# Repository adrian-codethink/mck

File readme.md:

# Modular choc Keeb

This is an attempt to make a 3 key module to allow custom angle and spacing of a column staggered ergonomic keyboard.

Initially this will make it relatively simple to string 6 of these together into a left or right hand 3x5 with a 3 button thumb cluster.

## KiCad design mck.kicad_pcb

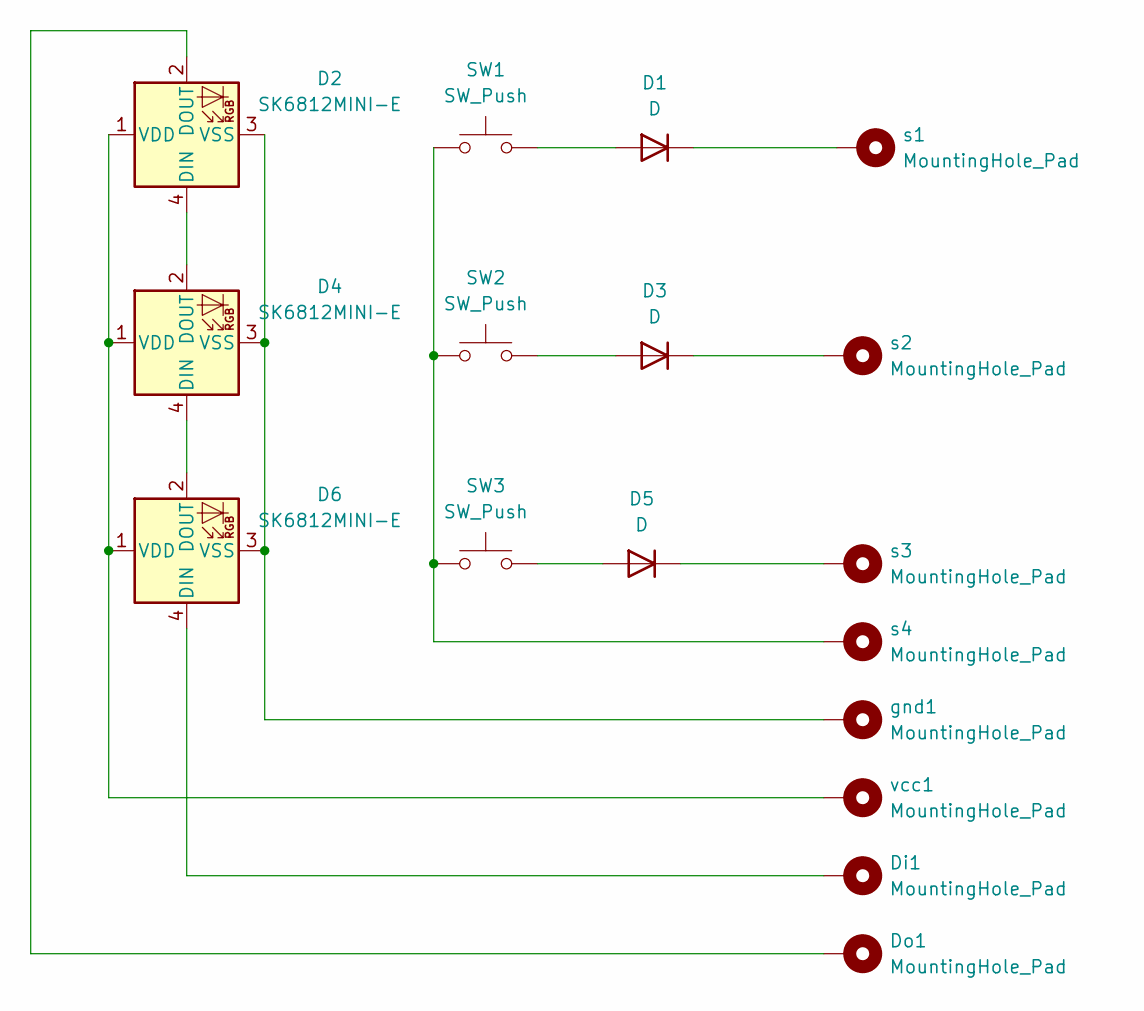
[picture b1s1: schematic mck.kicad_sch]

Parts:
D1, D3, D5: D; D_0805_2012Metric
D2, D4, D6: SK6812MINI-E; SK6812-MINI-E_v2
Di1: MountingHole_Pad; SolderWire-0.25sqmm_1x01_D0.65mm_OD1.7mm
Do1: MountingHole_Pad; SolderWire-0.25sqmm_1x01_D0.65mm_OD1.7mm
SW1, SW2, SW3: SW_Push; SW_Hotswap_Kailh_Choc_V1V2_1.00u
gnd1: MountingHole_Pad; SolderWire-0.25sqmm_1x01_D0.65mm_OD1.7mm
s1, s2, s3, s4: MountingHole_Pad; SolderWire-0.25sqmm_1x01_D0.65mm_OD1.7mm
vcc1: MountingHole_Pad; SolderWire-0.25sqmm_1x01_D0.65mm_OD1.7mm

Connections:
unnamed: D1.2 (A), SW1.1
unnamed: D1.1 (K), s1.1
unnamed: D2.4 (DIN), D4.2 (DOUT)
unnamed: D2.2 (DOUT), Do1.1
unnamed: D2.1 (VDD), D4.1 (VDD), D6.1 (VDD), vcc1.1
unnamed: D2.3 (VSS), D4.3 (VSS), D6.3 (VSS), gnd1.1
unnamed: D3.2 (A), SW2.1
unnamed: D3.1 (K), s2.1
unnamed: D4.4 (DIN), D6.2 (DOUT)
unnamed: D5.2 (A), SW3.1
unnamed: D5.1 (K), s3.1
unnamed: D6.4 (DIN), Di1.1
unnamed 12: SW1.2, SW2.2, SW3.2, s4.1; also elsewhere on the board

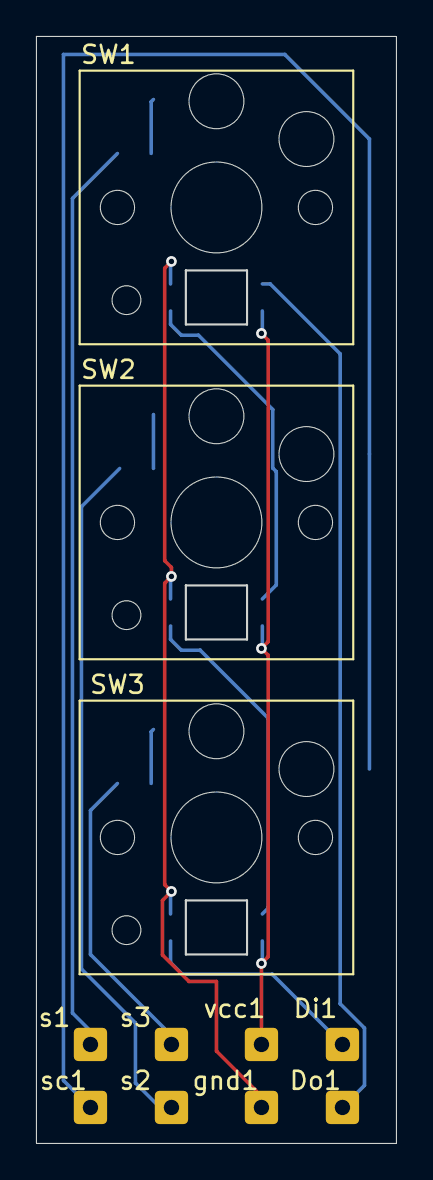
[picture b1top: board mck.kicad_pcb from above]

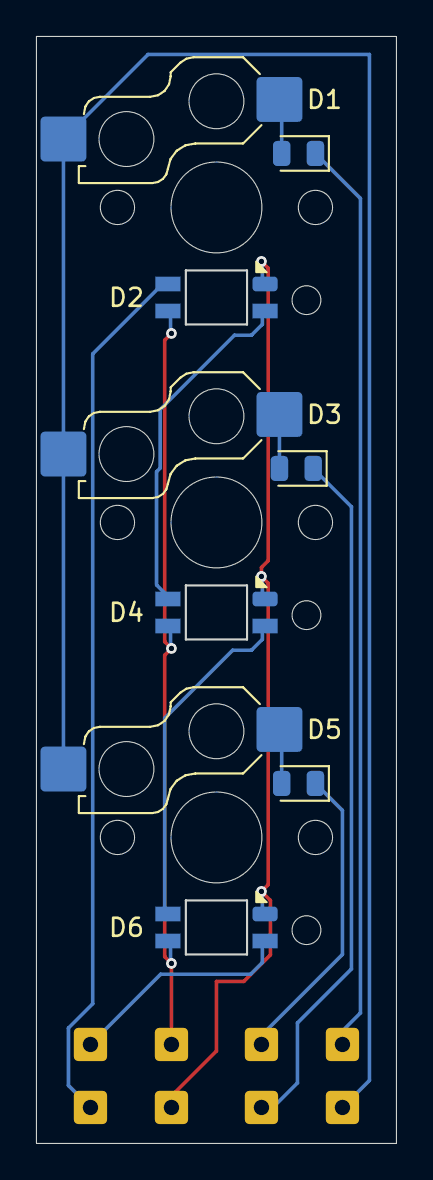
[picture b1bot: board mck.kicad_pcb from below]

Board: 2 copper layers, 19.9 x 61.4 mm, 17 parts (6 on the bottom side), 13 nets.

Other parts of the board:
sc1: MountingHole_Pad; SolderWire-0.25sqmm_1x01_D0.65mm_OD1.7mm

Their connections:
unnamed 12: sc1.1; also elsewhere on the board
